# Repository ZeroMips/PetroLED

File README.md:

# PetroLED

This is a PCB-design for a LED filament driver that fits into a Feuerhand Atom lantern.
It is powered by a single AAA battery cell. To get the 70V for the filament, it uses a joule thief circuit.
The design is heavily inspired by this article: https://www.instructables.com/Joule-Thief-Filament/
Production data is prepared for JLCPCB including assembly.

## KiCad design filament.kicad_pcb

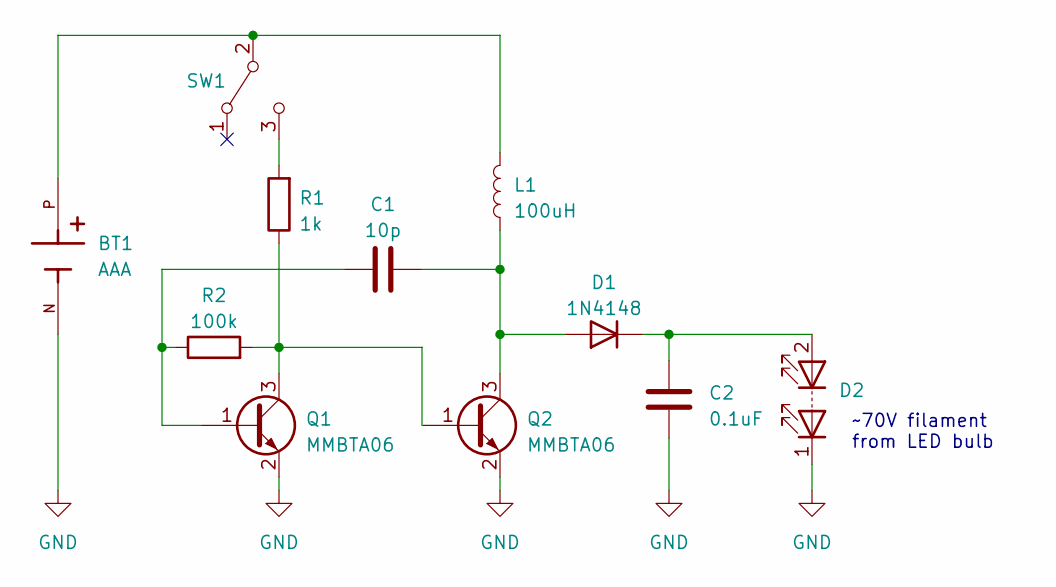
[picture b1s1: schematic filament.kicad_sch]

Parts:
BT1: AAA; BAT_1021; PARTREV A
C1: 10p; C_0603_1608Metric; LCSC C1634
C2: 0.1uF; C_0805_2012Metric; Voltage 100V; LCSC C28233
D1: 1N4148; D_SOD-123; LCSC C81598
D2: LED_Series; Filament
L1: 100uH; L_Bourns-SRN8040_8x8.15mm; LCSC C5127433
Q1, Q2: MMBTA06; SOT-23; LCSC C713285
R1: 1k; R_0805_2012Metric; LCSC C17513
R2: 100k; R_0805_2012Metric; LCSC C149504
SW1: SW_SPST; SSSS811101; LCSC C109335

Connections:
GND: BT1.N, C2.2, D2.1 (K), Q1.2 (E), Q2.2 (E)
unnamed: C1.2, D1.2 (A), L1.1, Q2.3 (C)
unnamed: C2.1, D1.1 (K), D2.2 (A)
unnamed: C1.1, Q1.1 (B), R2.1
unnamed: Q1.3 (C), Q2.1 (B), R1.1, R2.2
unnamed: BT1.P, L1.2, SW1.2 (B)
unnamed: R1.2, SW1.3 (C)

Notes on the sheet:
~70V filament from LED bulb

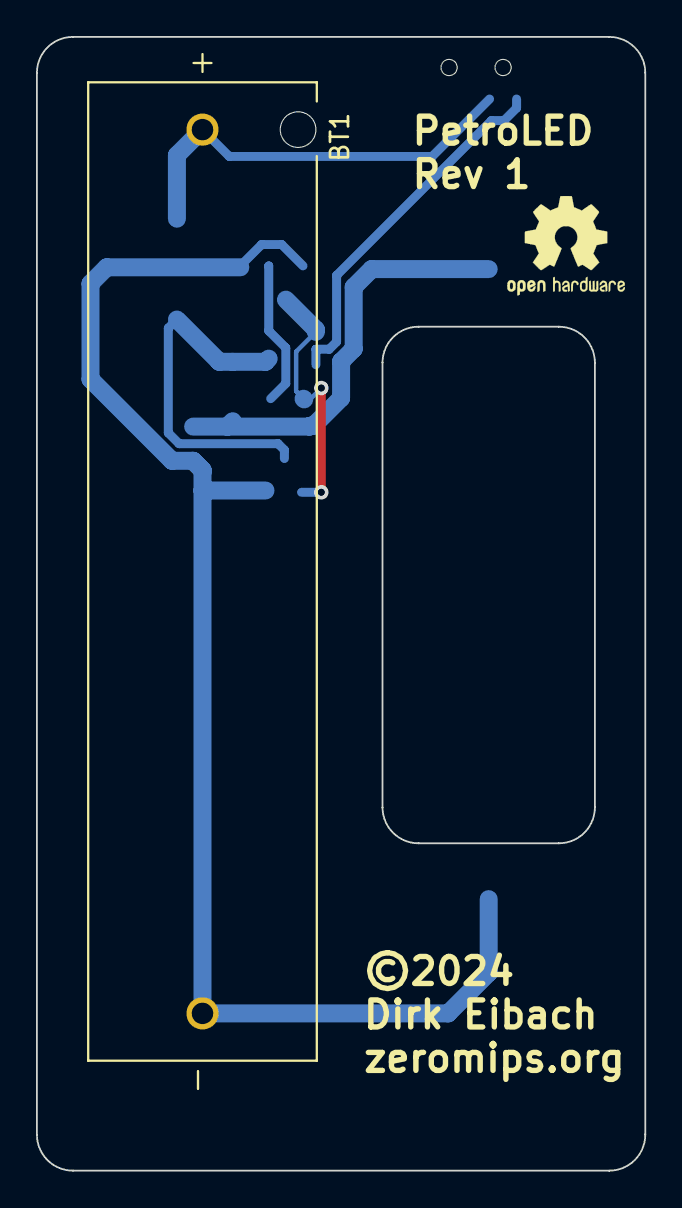
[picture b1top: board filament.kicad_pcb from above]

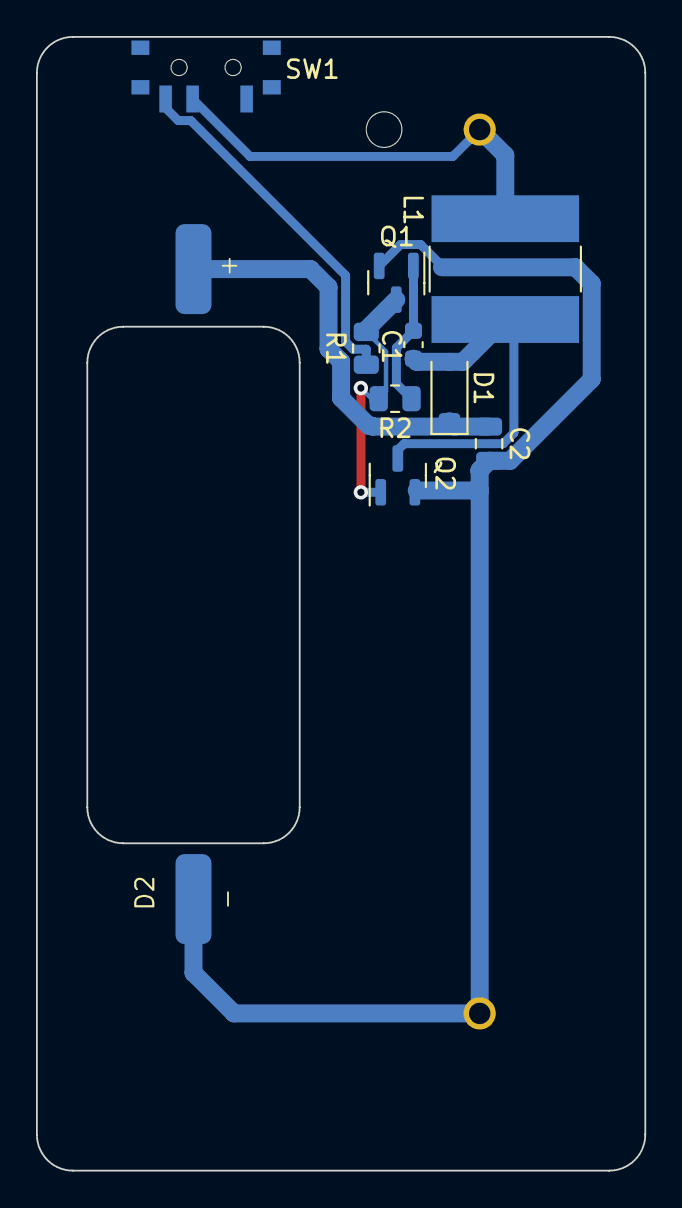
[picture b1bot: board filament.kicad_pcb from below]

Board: 2 copper layers, 33.8 x 63.0 mm, 11 parts (10 on the bottom side), 7 nets.

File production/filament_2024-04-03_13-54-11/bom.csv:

Designator,Footprint,Quantity,Value,LCSC Part #
BT1,BAT_1021,1,AAA,
C1,0603,1,10p,C1634
C2,0805,1,0.1uF,C28233
D1,D_SOD-123,1,1N4148,C81598
D2,Filament,1,LED_Series,
L1,L_Bourns-SRN8040_8x8.15mm,1,100uH,C5127433
"Q1, Q2",SOT-23,2,MMBTA06,C713285
R1,0805,1,1k,C17513
R2,0805,1,100k,C149504
SW1,SSSS811101,1,SW_SPST,C109335

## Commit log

2024-04-05 initial checkin
2024-04-05 Add images to README.md

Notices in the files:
filament.kicad_pcb:
©2024
